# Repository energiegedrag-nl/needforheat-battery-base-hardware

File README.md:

# NeedForHeat BatteryBASE

Open hardware for the **NeedForHeat BatteryBASE**: an extension for the M5Stack CoreInk that holds three AAA cells
(alkaline or NiMH rechargeable) to extend the battery life of the NeedForHeat living-room module.

**Status: prototype design.** Circuit, simulation, PCB and enclosure are designed (see
[docs/design.md](./docs/design.md)); nothing has been built yet. The original requirements are in
[docs/design-brief.md](./docs/design-brief.md).

## Table of contents
* [General info](#general-info)
* [Producing](#producing)
* [Deploying](#deploying)
  * [Cost](#cost)
* [Developing](#developing)
* [Status](#status)
* [License](#license)
* [Credits](#credits)

## General info

The cells do not power the CoreInk directly: they charge the CoreInk's internal LiPo battery at a low, constant
current through the `BAT` pin of the CoreInk bus. The LiPo supplies the current peaks of Wi-Fi, which AAA cells
cannot deliver. The firmware recognises the BatteryBASE, estimates the remaining energy and warns in time to replace
or recharge the cells.

The BatteryBASE is the end item of a stack: it fits directly on a CoreInk, or behind a
[NeedForHeat P1-BASE v3](https://github.com/energiegedrag-nl/needforheat-p1-base-hardware).

Firmware support is planned in [needforheat-generic-firmware](https://github.com/energiegedrag-nl/needforheat-generic-firmware),
the shared library of the NeedForHeat device firmware.

## Producing

### Printed Circuit Board

The folder [pcb/jlcpcb](./pcb/jlcpcb) contains the files to have the PCB manufactured *and assembled* by
[JLCPCB](https://jlcpcb.com):

1. Upload [`GERBER-needforheat-battery-base-hardware.zip`](./pcb/jlcpcb/GERBER-needforheat-battery-base-hardware.zip)
   on the [JLCPCB quote page](https://cart.jlcpcb.com/quote). Defaults are fine (2 layers, 1.6 mm), except the
   surface finish: **LF-HASL** (lead-free HASL) instead of OSP; the contacts' pins are soldered after two reflow
   passes, when OSP wets worst.
2. Select *PCB Assembly* and upload
   [`BOM-needforheat-battery-base-hardware.csv`](./pcb/jlcpcb/BOM-needforheat-battery-base-hardware.csv) and
   [`CPL-needforheat-battery-base-hardware.csv`](./pcb/jlcpcb/CPL-needforheat-battery-base-hardware.csv).
   JLCPCB offers *Standard* PCBA only for this board; the 2x8 header (through-hole) is soldered by JLCPCB as well.
3. Select *Assemble both sides*: the six battery contacts (MYOUNG MY-AAA-01 leaf contacts, C964855) sit on the other
   side of the board and are in the BOM and the placement file (THT, soldered by JLCPCB). Their 1.5 mm pins end just
   inside the 1.6 mm board; add the order remark: *"BC1-BC6 (C964855): please make sure the solder flows through to
   the pads on the other side (bottom side, where the contact's foot rests)."*

Schematic and layout printouts: [docs/needforheat-battery-base-hardware-sch.pdf](docs/needforheat-battery-base-hardware-sch.pdf)
and [docs/needforheat-battery-base-hardware-pcb.pdf](docs/needforheat-battery-base-hardware-pcb.pdf). Simulation
results (charge control, off-state currents): [docs/simulation](docs/simulation/README.md).

### Enclosure

The folder [enclosure/fabrication](./enclosure/fabrication) contains the tray (*kuip*), the sliding lid and the cradle
(STEP and STL), generated by [enclosure/kuip.py](enclosure/kuip.py); see [enclosure/README.md](enclosure/README.md).
Print them in MJF nylon (PA12) or PETG. For a first print, order the second lid `battery-base-lid-loose` (more play)
along with the rest, in case the normal lid is too tight.

## Deploying

### Cost

Indicative, November 2026, excluding VAT and shipping. JLCPCB quotes of 17 November 2026 (Standard PCBA, **both
sides**, LF-HASL, edge rails added by JLCPCB, no panelisation) and JLC3DP quotes (MJF PA12-HP, dyed black) for the same
quantities as the [P1-BASE](https://github.com/energiegedrag-nl/needforheat-p1-base-hardware#cost):

| Quantity | PCB | PCBA | Total PCB + PCBA | Per board | Enclosure (tray, lid, cradle) per set |
|---:|---:|---:|---:|---:|---:|
| 5 | € 4.72 | € 135.21 | € 139.93 | € 27.99 | $ 4.57 |
| 10 | € 5.72 | € 159.59 | € 165.31 | € 16.53 | $ 4.57 |
| 30 | € 18.26 | € 267.91 | € 286.17 | € 9.54 | $ 4.57 |
| 100 | € 48.88 | € 593.85 | € 642.73 | € 6.43 | $ 4.57 |

About € 96 of every PCBA order is fixed: setup for two sides € 46.79, stencil € 7.51, the loading fee for the
extended parts € 26.76 and the assembly fixture for the through-hole parts € 15.03 (more for larger orders). That is
why small orders are expensive per board. The components cost € 6.16 per board at 5 boards (JLCPCB buys minimum
quantities) and € 3.90 at 100; the most expensive are the ADS1115 (U5) and the PCA9536 (U6), about € 1.10 each at 5
pieces; the six MY-AAA-01 contacts cost about € 0.11 each. Soldering the contacts and the header by hand adds about
€ 6 at 5 boards (hand-soldering € 3.28, manual assembly € 3.06). LF-HASL instead of OSP adds € 1.09 at 5 boards and
€ 6.81 at 100. Not included: the three AAA cells and shipping (DHL, about € 21–25 per order for PCBs, about $ 6.50
for the prints).

Enclosure per set (JLC3DP, re-quoted 17 November 2026 with the review fixes): tray $ 2.04, lid $ 1.48, cradle $ 1.05.
The spare lid with more play (`battery-base-lid-loose`) for a first print costs $ 1.46.

## Developing

The design is generated with scripts in [tools](./tools), like the P1-BASE v3: KiCad schematic and PCB, autorouting
with Freerouting, ngspice simulations, independent checks, and a parametric CadQuery enclosure. Open work is in
[TODO.md](TODO.md).

* **Enclosure first**: `python enclosure/kuip.py` (CadQuery) builds the tray, lid and cradle and writes
  `enclosure/pcb_constraints.json` (contact places, keep-outs) for the PCB. `python enclosure/check_fit.py >
  enclosure/fit-check.txt` checks every part against the others, including the real leaf contacts (the vendor's 3D
  model, free and pressed by the shortest and longest cell, `enclosure/check_leaf.py`).
* **PCB** (KiCad 10's Python, `%LOCALAPPDATA%\Programs\KiCad\10.0\bin\python.exe`): `tools/gen_footprints.py`,
  `tools/gen_schematic.py`, then `tools/gen_pcb.py` places and routes (Freerouting, a few GB of memory; best from a
  plain PowerShell window). Try `BBASE_VARIANT` 0..5 until the log shows `(0 unrouted`. After a small change, route
  lightly instead (a few minutes, 1 GB): `gen_pcb.py --move-contacts` puts the contacts at their places from
  `pcb_constraints.json` and re-routes only their tracks; `gen_pcb.py --reroute NET,NET` rips up and routes only those
  nets, with the rest locked. (In Git Bash set `MSYS_NO_PATHCONV=1`, or net names such as `/EN` turn into paths.)
* **Finish and check**: `tools/pcb_cleanup.py`, `kicad-cli pcb drc --refill-zones --save-board --schematic-parity`,
  `tools/pcb_bridge_gnd.py` for GND islands left after routing, and `python tools/export_fab.py` for the Gerbers, BOM,
  CPL, PDFs, renders and the PCB's STEP.
* **3D models**: `tools/gen_3d_models.py` (header) and `tools/import_leaf_model.py <step>` (places the vendor's model
  of the MY-AAA-01 from LCSC/EasyEDA in the footprint's frame).

## Status

Project is _in progress_ (prototype design, not yet built).

## License

The hardware designs in this repository are available under the [CERN-OHL-P v2 license](./LICENSE),
Copyright 2026 Henri ter Hofte.

## Credits

Designed by:
* Henri ter Hofte · [@henriterhofte](https://github.com/henriterhofte)

The BatteryBASE builds on the NeedForHeat P1-BASE and other NeedForHeat hardware, originally developed by the
Research group Energy Transition of Windesheim University of Applied Sciences.

### AI assistance

Parts of this repository were made with [Claude Code](https://claude.com/claude-code) (Anthropic), under the author's
direction and review. Commits made this way carry a `Co-Authored-By:` trailer. The author remains responsible for all
content.

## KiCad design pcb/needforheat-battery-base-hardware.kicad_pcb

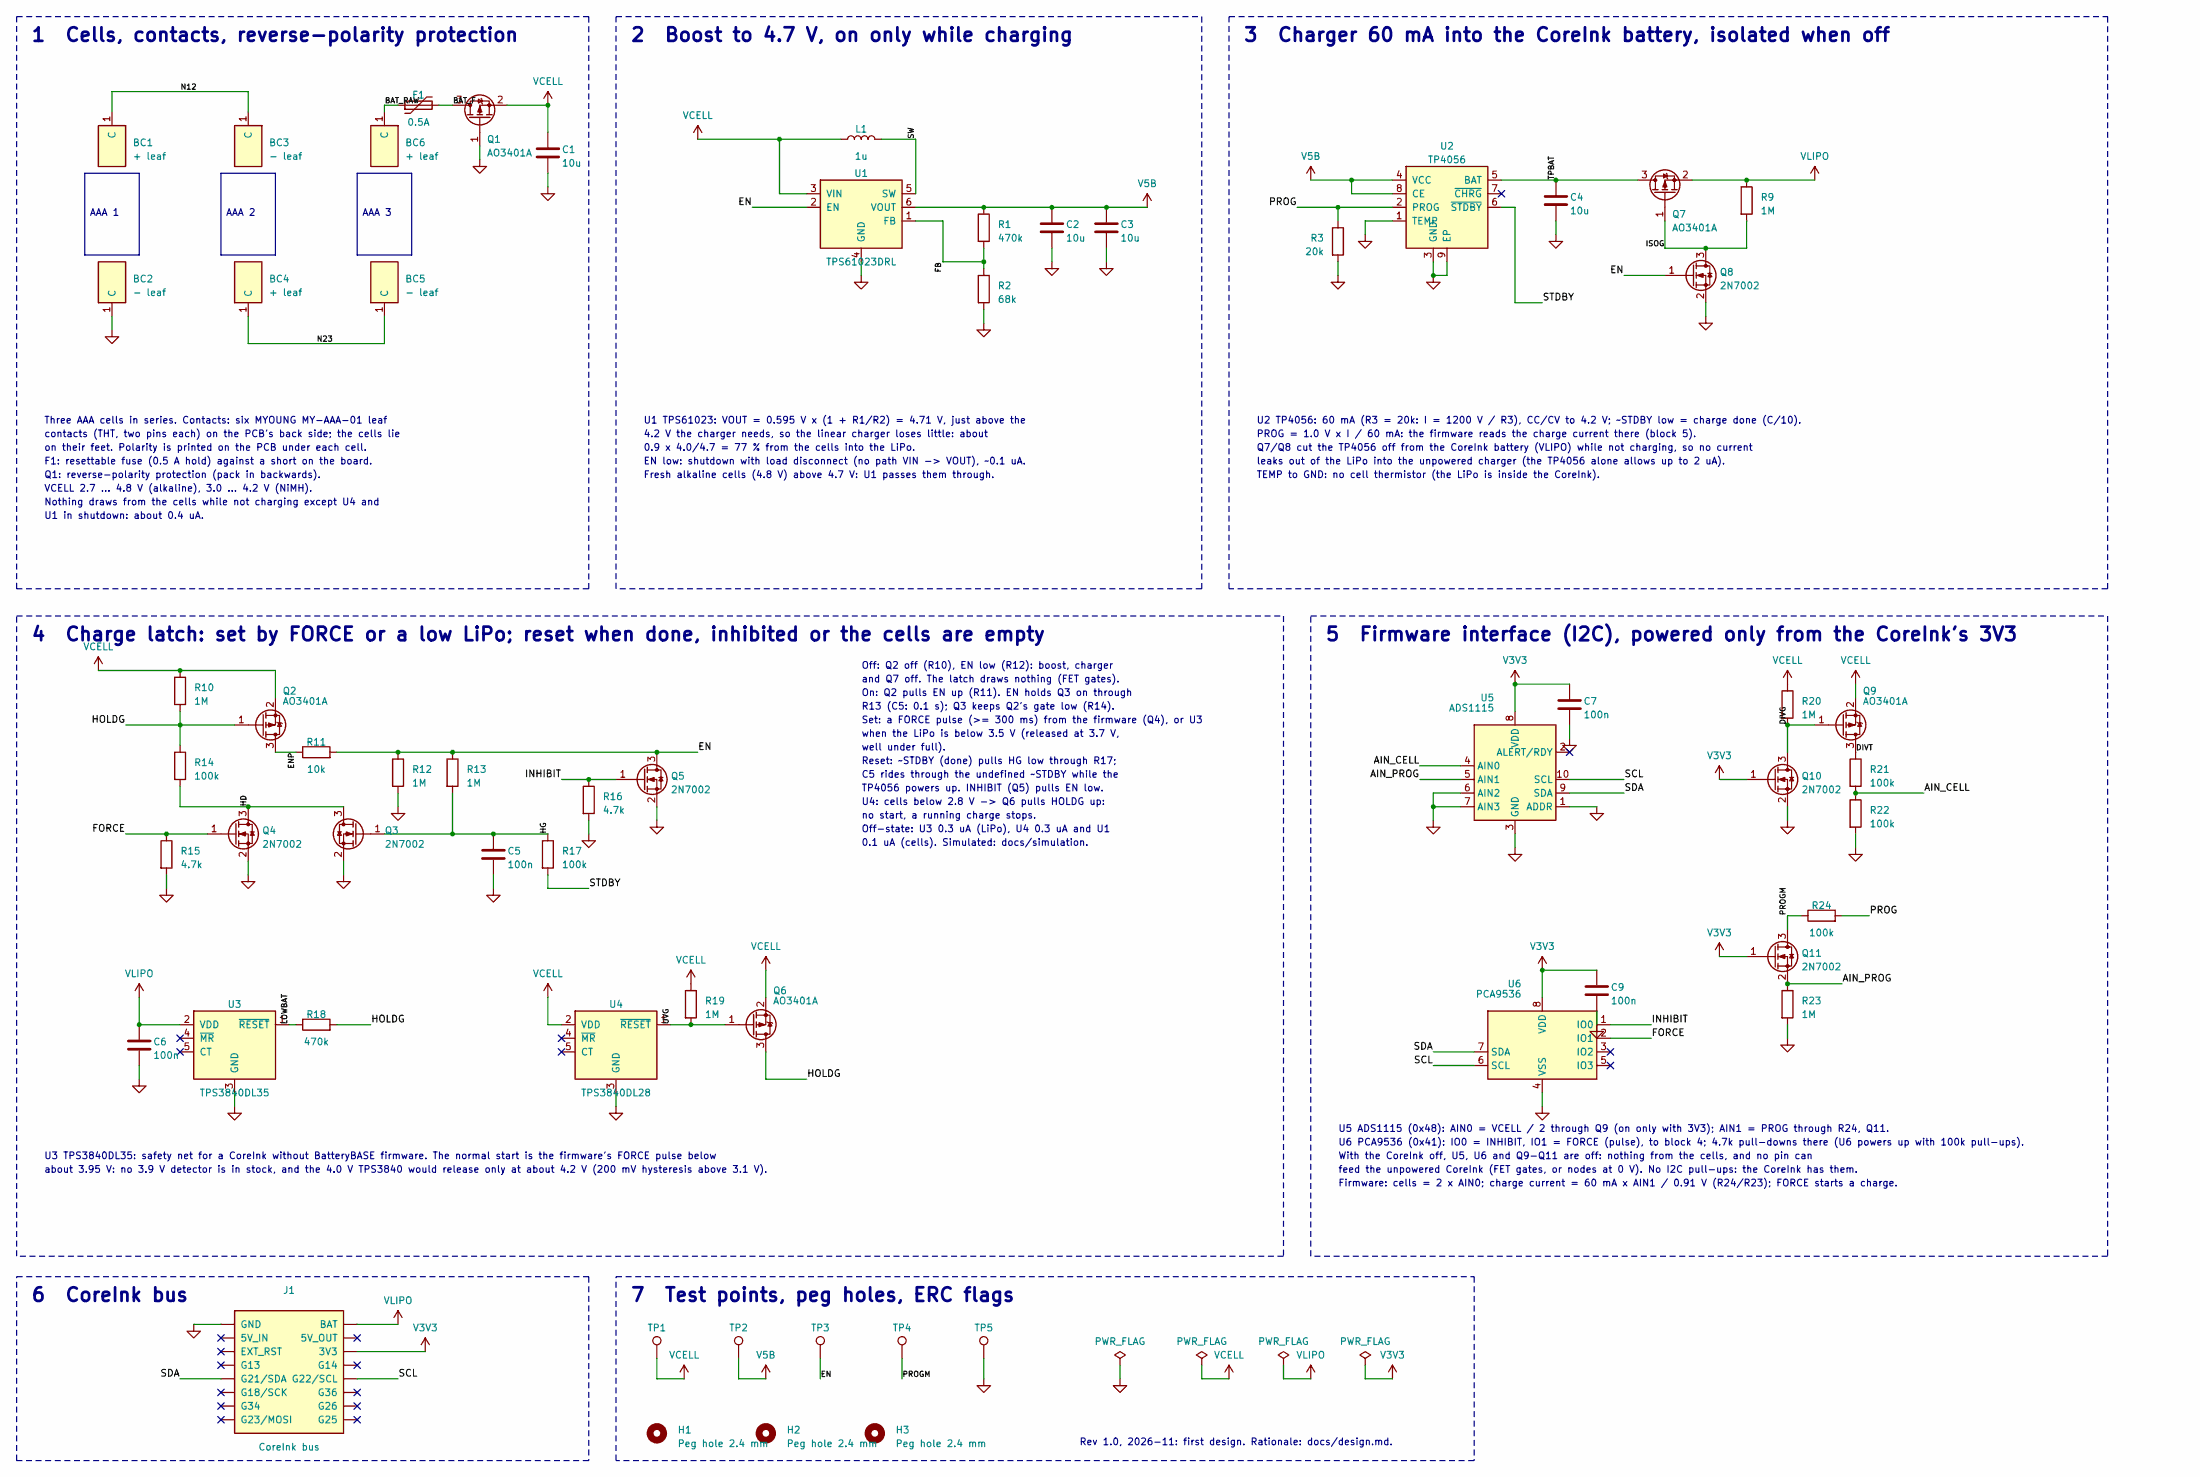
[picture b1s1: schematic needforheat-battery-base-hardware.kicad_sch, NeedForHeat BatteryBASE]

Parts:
BC1, BC4, BC6: + leaf; MYOUNG_MY-AAA-01; LCSC C964855
BC2, BC3, BC5: - leaf; MYOUNG_MY-AAA-01; LCSC C964855
C1, C2, C3, C4: 10u; C_0805_2012Metric; LCSC C15850
C5, C6, C7, C9: 100n; C_0603_1608Metric; LCSC C14663
F1: 0.5A; Fuse_0805_2012Metric; LCSC C269104
H1, H2, H3: Peg hole 2.4 mm; PegHole_2.4mm_NPTH
J1: CoreInk bus; CoreInk_Bus_2x08_P2.54mm; LCSC C706898
L1: 1u; L_Sunlord_SWPA3015S; LCSC C43388
Q1, Q2, Q6, Q7, Q9: AO3401A; SOT-23; LCSC C15127
Q3, Q4, Q5, Q8, Q10, Q11: 2N7002; SOT-23; LCSC C8545
R1, R18: 470k; R_0603_1608Metric; LCSC C23178
R2: 68k; R_0603_1608Metric; LCSC C23231
R3: 20k; R_0603_1608Metric; LCSC C4184
R9, R10, R12, R13, R19, R20, R23: 1M; R_0603_1608Metric; LCSC C22935
R11: 10k; R_0603_1608Metric; LCSC C25804
R14, R17, R21, R22, R24: 100k; R_0603_1608Metric; LCSC C25803
R15, R16: 4.7k; R_0603_1608Metric; LCSC C23162
TP1: VCELL; TestPoint_Pad_D1.0mm
TP2: V5B; TestPoint_Pad_D1.0mm
TP3: EN; TestPoint_Pad_D1.0mm
TP4: PROGM; TestPoint_Pad_D1.0mm
TP5: GND; TestPoint_Pad_D1.0mm
U1: TPS61023DRL; SOT-563; LCSC C919459
U2: TP4056; SOIC-8-1EP_3.9x4.9mm_P1.27mm_EP2.29x3mm; LCSC C16581
U3: TPS3840DL35; SOT-23-5; LCSC C2866251
U4: TPS3840DL28; SOT-23-5; LCSC C2066416
U5: ADS1115; MSOP-10_3x3mm_P0.5mm; LCSC C37593
U6: PCA9536; VSSOP-8_3x3mm_P0.65mm; LCSC C2649389

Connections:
/AIN_CELL: R21.2, R22.1, U5.4 (AIN0)
/AIN_PROG: Q11.2 (S), R23.1, U5.5 (AIN1)
/BAT_F: F1.2, Q1.3 (D)
/BAT_RAW: BC6.1, F1.1
/DIVG: Q9.1 (G), Q10.3 (D), R20.2
/DIVT: Q9.3 (D), R21.1
/EN: Q5.3 (D), Q8.1 (G), R11.2, R12.1, R13.1, TP3.1, U1.2 (EN)
/ENP: Q2.3 (D), R11.1
/FB: R1.2, R2.1, U1.1 (FB)
/FORCE: Q4.1 (G), R15.1, U6.2 (IO1)
/HD: Q3.3 (D), Q4.3 (D), R14.2
/HG: C5.1, Q3.1 (G), R13.2, R17.1
/HOLDG: Q2.1 (G), Q6.3 (D), R10.2, R14.1, R18.2
/INHIBIT: Q5.1 (G), R16.1, U6.1 (IO0)
/ISOG: Q7.1 (G), Q8.3 (D), R9.2
/LOWBAT: R18.1, U3.1 (~RESET)
/N12: BC1.1, BC3.1
/N23: BC4.1, BC5.1
/PROG: R3.1, R24.2, U2.2 (PROG)
/PROGM: Q11.3 (D), R24.1, TP4.1
/SCL: J1.G22 (G22/SCL), U5.10 (SCL), U6.6 (SCL)
/SDA: J1.G21 (G21/SDA), U5.9 (SDA), U6.7 (SDA)
/STDBY: R17.2, U2.6 (~STDBY)
/SW: L1.2, U1.5 (SW)
/TPBAT: C4.1, Q7.3 (D), U2.5 (BAT)
/UVG: Q6.1 (G), R19.2, U4.1 (~RESET)
GND: BC2.1, C1.2, C2.2, C3.2, C4.2, C5.2, C6.2, C7.2, C9.2, J1.GND, Q1.1 (G), Q3.2 (S), Q4.2 (S), Q5.2 (S), Q8.2 (S), Q10.2 (S), R2.2, R3.2, R12.2, R15.2, R16.2, R22.2, R23.2, TP5.1, U1.4 (GND), U2.1 (TEMP), U2.3 (GND), U2.9 (EP), U3.3 (GND), U4.3 (GND), U5.1 (ADDR), U5.3 (GND), U5.6 (AIN2), U5.7 (AIN3), U6.4 (VSS)
V3V3: C7.1, C9.1, J1.3V3, Q10.1 (G), Q11.1 (G), U5.8 (VDD), U6.8 (VDD)
V5B: C2.1, C3.1, R1.1, TP2.1, U1.6 (VOUT), U2.4 (VCC), U2.8 (CE)
VCELL: C1.1, L1.1, Q1.2 (S), Q2.2 (S), Q6.2 (S), Q9.2 (S), R10.1, R19.1, R20.1, TP1.1, U1.3 (VIN), U4.2 (VDD)
VLIPO: C6.1, J1.BAT, Q7.2 (S), R9.1, U3.2 (VDD)

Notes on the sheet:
1 Cells, contacts, reverse-polarity protection
AAA 1
AAA 2
AAA 3
Three AAA cells in series. Contacts: six MYOUNG MY-AAA-01 leaf
contacts (THT, two pins each) on the PCB's back side; the cells lie
on their feet. Polarity is printed on the PCB under each cell.
F1: resettable fuse (0.5 A hold) against a short on the board.
Q1: reverse-polarity protection (pack in backwards).
VCELL 2.7 ... 4.8 V (alkaline), 3.0 ... 4.2 V (NiMH).
Nothing draws from the cells while not charging except U4 and
U1 in shutdown: about 0.4 uA.
2 Boost to 4.7 V, on only while charging
U1 TPS61023: VOUT = 0.595 V x (1 + R1/R2) = 4.71 V, just above the
4.2 V the charger needs, so the linear charger loses little: about
0.9 x 4.0/4.7 = 77 % from the cells into the LiPo.
EN low: shutdown with load disconnect (no path VIN -> VOUT), ~0.1 uA.
Fresh alkaline cells (4.8 V) above 4.7 V: U1 passes them through.
3 Charger 60 mA into the CoreInk battery, isolated when off
U2 TP4056: 60 mA (R3 = 20k: I = 1200 V / R3), CC/CV to 4.2 V; ~STDBY low = charge done (C/10).
PROG = 1.0 V x I / 60 mA: the firmware reads the charge current there (block 5).
Q7/Q8 cut the TP4056 off from the CoreInk battery (VLIPO) while not charging, so no current
leaks out of the LiPo into the unpowered charger (the TP4056 alone allows up to 2 uA).
TEMP to GND: no cell thermistor (the LiPo is inside the CoreInk).
4 Charge latch: set by FORCE or a low LiPo; reset when done, inhibited or the cells are empty
Off: Q2 off (R10), EN low (R12): boost, charger
and Q7 off. The latch draws nothing (FET gates).
On: Q2 pulls EN up (R11). EN holds Q3 on through
R13 (C5: 0.1 s); Q3 keeps Q2's gate low (R14).
Set: a FORCE pulse (>= 300 ms) from the firmware (Q4), or U3
when the LiPo is below 3.5 V (released at 3.7 V,
well under full).
Reset: ~STDBY (done) pulls HG low through R17;
C5 rides through the undefined ~STDBY while the
TP4056 powers up. INHIBIT (Q5) pulls EN low.
U4: cells below 2.8 V -> Q6 pulls HOLDG up:
no start, a running charge stops.
Off-state: U3 0.3 uA (LiPo), U4 0.3 uA and U1
0.1 uA (cells). Simulated: docs/simulation.
U3 TPS3840DL35: safety net for a CoreInk without BatteryBASE firmware. The normal start is the firmware's FORCE pulse below

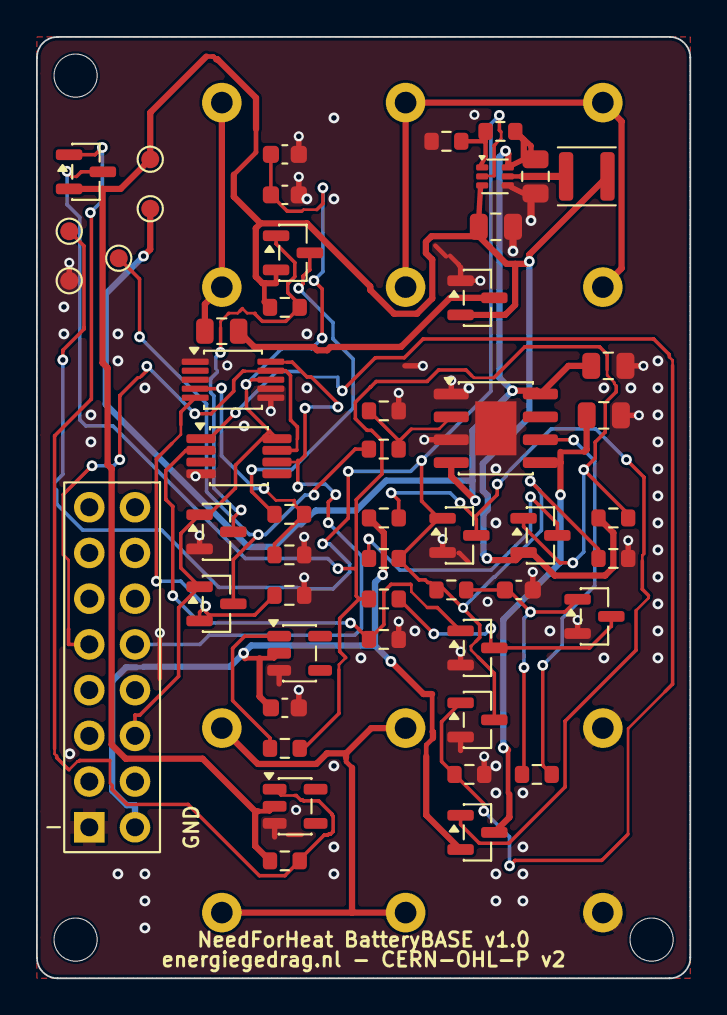
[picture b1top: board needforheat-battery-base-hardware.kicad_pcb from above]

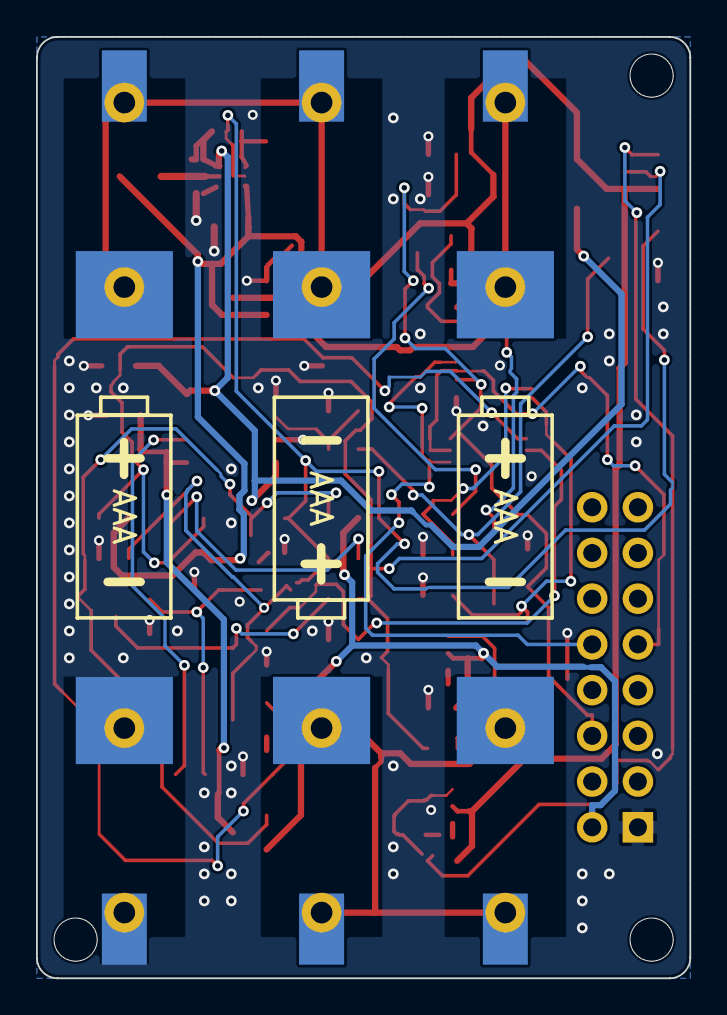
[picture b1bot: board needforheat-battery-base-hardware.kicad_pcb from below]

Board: 2 copper layers, 36.3 x 52.3 mm, 61 parts (6 on the bottom side), 31 nets.

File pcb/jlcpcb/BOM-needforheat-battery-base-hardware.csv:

Comment,Designator,Footprint,LCSC
+ leaf / - leaf,"BC1,BC4,BC6,BC2,BC3,BC5",MYOUNG_MY-AAA-01,C964855
10u,"C1,C2,C3,C4",C_0805_2012Metric,C15850
100n,"C5,C6,C7,C9",C_0603_1608Metric,C14663
0.5A,F1,Fuse_0805_2012Metric,C269104
CoreInk bus,J1,CoreInk_Bus_2x08_P2.54mm,C706898
1u,L1,L_Sunlord_SWPA3015S,C43388
AO3401A,"Q1,Q2,Q6,Q7,Q9",SOT-23,C15127
2N7002,"Q3,Q4,Q5,Q8,Q10,Q11",SOT-23,C8545
470k,"R1,R18",R_0603_1608Metric,C23178
68k,R2,R_0603_1608Metric,C23231
20k,R3,R_0603_1608Metric,C4184
1M,"R9,R10,R12,R13,R19,R20,R23",R_0603_1608Metric,C22935
10k,R11,R_0603_1608Metric,C25804
100k,"R14,R17,R21,R22,R24",R_0603_1608Metric,C25803
4.7k,"R15,R16",R_0603_1608Metric,C23162
TPS61023DRL,U1,SOT-563,C919459
TP4056,U2,SOIC-8-1EP_3.9x4.9mm_P1.27mm_EP2.29x3mm,C16581
TPS3840DL35,U3,SOT-23-5,C2866251
TPS3840DL28,U4,SOT-23-5,C2066416
ADS1115,U5,MSOP-10_3x3mm_P0.5mm,C37593
PCA9536,U6,VSSOP-8_3x3mm_P0.65mm,C2649389

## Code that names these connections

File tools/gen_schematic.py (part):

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    s.place("R3", 261.62, 57.15, side="left")
    s.wire("U2.2", (261.62, 50.8), "R3.1", first="h")
    s.wire((261.62, 50.8), (254.0, 50.8))
    s.label("PROG", (254.0, 50.8), "l")
    gnd(s, "R3.2")
    s.wire("U2.1", (266.7, 53.34), (266.7, 55.88), first="h")
    s.power("GND", (266.7, 55.88))
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    gnd(s, "Q8.2")
    s.stub("Q8.1", "EN", 7.62, "l")
    s.wire("U2.6", (294.64, 50.8), (294.64, 68.58), (299.72, 68.58), first="h")
    s.label("STDBY", (299.72, 68.58), "r")
    s.label("ISOG", (322.58, 58.42), "l", 1.0)
    s.label("TPBAT", "C4.1", "u", 1.0)
    notes(s, 246.38, 91.44, [
        "U2 TP4056: 60 mA (R3 = 20k: I = 1200 V / R3), CC/CV to 4.2 V; ~STDBY low = charge done (C/10).",
        "PROG = 1.0 V x I / 60 mA: the firmware reads the charge current there (block 5).",
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    s.wire((45.72, 137.16), "R10.1")
    s.wire("R10.2", (45.72, 147.32), "Q2.1", first="v")
    s.wire((45.72, 147.32), (35.56, 147.32))
    s.label("HOLDG", (35.56, 147.32), "l")
    s.place("R11", 71.12, 152.4, rot=90)
    s.wire("Q2.3", "R11.1")
    s.place("R12", 86.36, 156.21)
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    s.place("R16", 121.92, 161.29)
    s.wire("Q5.1", (121.92, 157.48), (116.84, 157.48))
    s.wire((121.92, 157.48), "R16.1")
    s.label("INHIBIT", (116.84, 157.48), "l")
    gnd(s, "R16.2")
    # hold: EN -> R13 -> HG (C5) -> Q3 -> HD -> R14 -> HOLDG
    s.place("C5", 104.14, 171.45)
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    s.place("R17", 114.3, 171.45)
    s.wire((104.14, 167.64), "R17.1")
    s.wire("R17.2", (114.3, 177.8), (121.92, 177.8), first="v")
    s.label("STDBY", (121.92, 177.8), "r")
    s.place("R14", 45.72, 154.94)
    s.wire((45.72, 147.32), "R14.1")
    s.place("Q4", 55.88, 167.64)
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    s.wire("R14.2", (45.72, 162.56), "Q4.3", "Q3.3", first="v")
    s.wire("Q4.1", "R15.1")
    s.wire("R15.1", (35.56, 167.64))
    s.label("FORCE", (35.56, 167.64), "l")
    gnd(s, "R15.2")
    gnd(s, "Q4.2")
    s.label("HD", "Q4.3", "u", 1.0)
    # STDBY -> R17 -> HG
    s.label("HG", "R17.1", "u", 1.0)
    s.label("ENP", "R11.1", "d", 1.0)
    # safety net U3 on the LiPo, cells undervoltage U4 with Q6
    s.place("U3", 55.88, 205.74)
    s.place("C6", 38.1, 207.01)
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    s.place("R18", 71.12, 203.2, rot=90)
    s.wire("U3.1", (66.04, 203.2), "R18.1")
    s.wire("R18.2", (81.28, 203.2))
    s.label("HOLDG", (81.28, 203.2), "r")
    s.label("LOWBAT", (66.04, 203.2), "u", 1.0)
    s.place("U4", 127.0, 205.74)
    s.wire("U4.2", (114.3, 203.2), (114.3, 198.12), first="h")
    s.power("VCELL", (114.3, 198.12))
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    s.wire("Q6.2", (154.94, 193.04))
    s.power("VCELL", (154.94, 193.04))
    s.wire("Q6.3", (154.94, 213.36), (162.56, 213.36), first="v")
    s.label("HOLDG", (162.56, 213.36), "r")
    s.label("UVG", (137.16, 203.2), "u", 1.0)
    notes(s, 172.72, 137.16, [
        "Off: Q2 off (R10), EN low (R12): boost, charger",
        "and Q7 off. The latch draws nothing (FET gates).",
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    s.wire("R21.2", "R22.1")
    gnd(s, "R22.2")
    s.wire((358.14, 160.02), (370.84, 160.02))
    s.label("AIN_CELL", (370.84, 160.02), "r")
    s.label("DIVG", (345.44, 147.32), "u", 1.0)
    s.label("DIVT", "R21.1", "r", 1.0)
    # PROG switched by the 3V3 rail
    s.place("Q11", 342.9, 190.5)
    s.place("R24", 351.79, 182.88, rot=90)
    s.wire("Q11.3", (345.44, 182.88), "R24.1", first="v")
    s.wire("R24.2", (360.68, 182.88))
    s.label("PROG", (360.68, 182.88), "r")
    s.label("PROGM", (345.44, 182.88), "u", 1.0)
    s.wire("Q11.1", (332.74, 190.5))
    s.power("V3V3", (332.74, 190.5))
    s.place("R23", 345.44, 199.39)
    s.wire("Q11.2", "R23.1")
    gnd(s, "R23.2")
    s.wire("Q11.2", (355.6, 195.58))
    s.label("AIN_PROG", (355.6, 195.58), "r")
    # I/O expander
    s.place("U6", 299.72, 205.74)
    s.place("C9", 309.88, 196.85)
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

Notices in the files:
pcb/needforheat-battery-base-hardware.kicad_pcb:
energiegedrag.nl - CERN-OHL-P v2
pcb/needforheat-battery-base-hardware.kicad_sch:
Licensed under CERN-OHL-P v2
